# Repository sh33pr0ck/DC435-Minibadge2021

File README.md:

# DC435-Minibadge2021

Based on the minibadge by luke jenkins: https://github.com/lukejenkins/minibadge

Fits the 10x10 badge display as is and can fit the main badge - mini badge holder with some modifications.

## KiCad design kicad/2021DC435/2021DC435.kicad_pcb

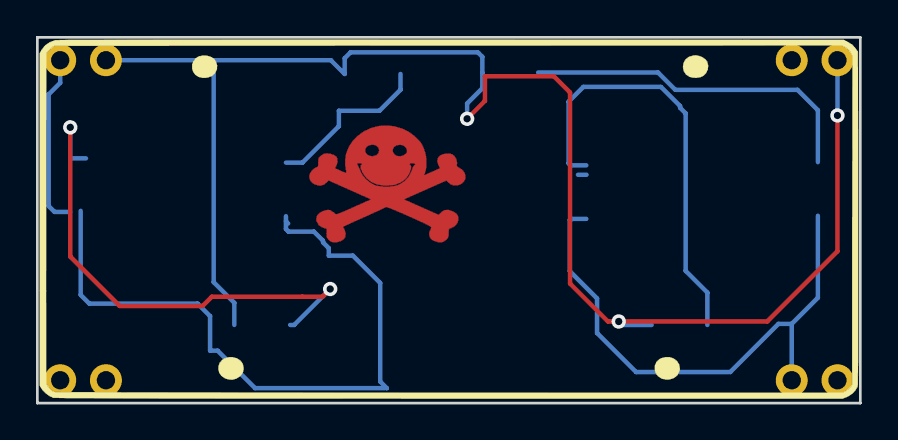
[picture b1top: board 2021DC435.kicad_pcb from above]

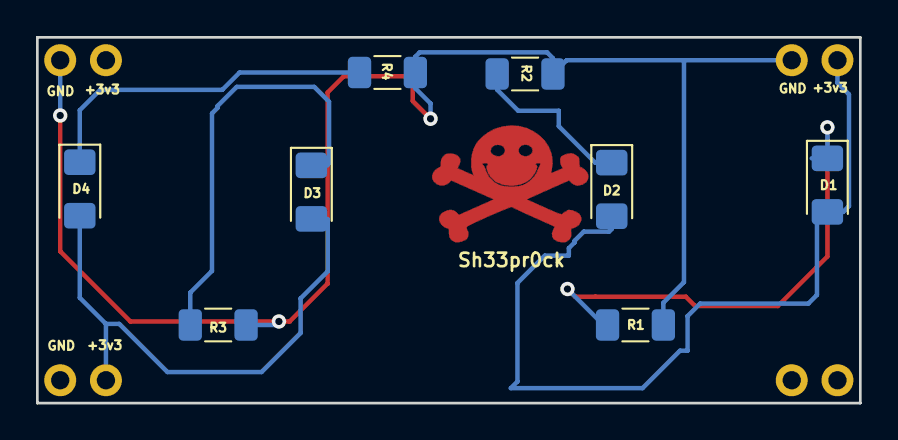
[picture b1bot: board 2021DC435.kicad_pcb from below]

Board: 2 copper layers, 45.7 x 20.3 mm, 9 parts (8 on the bottom side), 7 nets.

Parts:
D1, D2, D3, D4: LED; LED_1206_3216Metric_Pad1.42x1.75mm_HandSolder
R1, R2, R3, R4: R; R_1206_3216Metric_Pad1.30x1.75mm_HandSolder
X1: SAINTCON-Minibadge-Simple; SAINTCON-Minibadge-Doublewide

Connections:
unnamed: D1.1, R1.2
unnamed: D1.2, D2.2, X1.1
unnamed: D2.1, R2.2
unnamed: D3.1, R3.2
unnamed: D3.2, D4.2, X1.15
unnamed: D4.1, R4.2
unnamed: R1.1, R2.1, R3.1, R4.1, X1.2, X1.8

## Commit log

2022-07-20 Added Kicad and readme
